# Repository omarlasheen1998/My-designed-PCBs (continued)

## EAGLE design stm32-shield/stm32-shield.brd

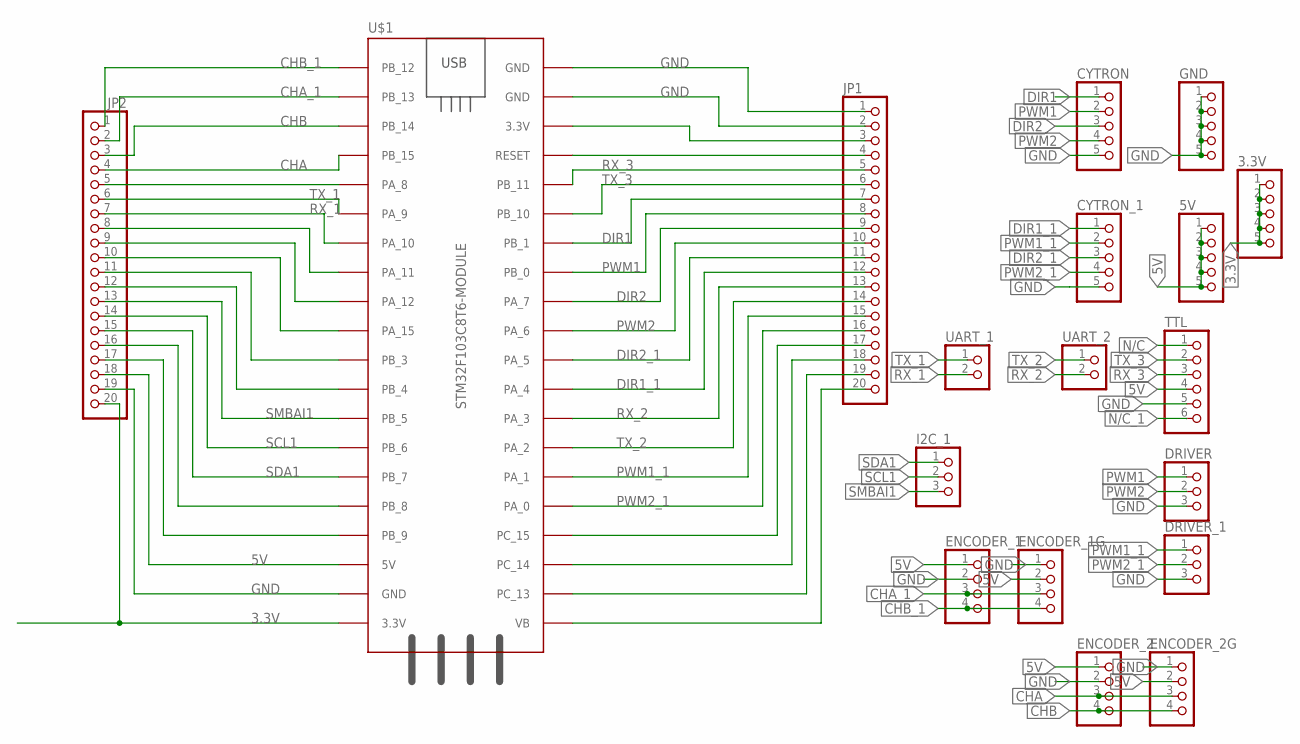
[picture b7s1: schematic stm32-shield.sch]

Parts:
3.3V, 5V: PINHD-1X5; 1X05
CYTRON: PINHD-1X5; 1X05
CYTRON_1: PINHD-1X5; 1X05
DRIVER: PINHD-1X3; 1X03
DRIVER_1: PINHD-1X3; 1X03
ENCODER_1, ENCODER_1G, ENCODER_2, ENCODER_2G: PINHD-1X4; 1X04
GND: PINHD-1X5; 1X05
I2C_1: PINHD-1X3; 1X03
JP1, JP2: PINHD-1X20; 1X20
TTL: PINHD-1X6; 1X06
U$1: STM32F103C8T6-MODULE
UART_1, UART_2: PINHD-1X2; 1X02

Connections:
3.3V: 3.3V.1, 3.3V.2, 3.3V.3, 3.3V.4, 3.3V.5, JP2.20, U$1.3.3V_1 (3.3V)
5V: 5V.1, 5V.2, 5V.3, 5V.4, 5V.5, ENCODER_1.1, ENCODER_1G.2, ENCODER_2.1, ENCODER_2G.2, JP2.18, TTL.4, U$1.5V
8183: JP2.17, U$1.PB_9
823828: JP2.16, U$1.PB_8
CHA: ENCODER_2.3, ENCODER_2G.3, JP2.4, U$1.PB_15
CHA_1: ENCODER_1.3, ENCODER_1G.3, JP2.2, U$1.PB_13
CHB: ENCODER_2.4, ENCODER_2G.4, JP2.3, U$1.PB_14
CHB_1: ENCODER_1.4, ENCODER_1G.4, JP2.1, U$1.PB_12
DIR1: CYTRON.1, JP1.7, U$1.PB_1
DIR1_1: CYTRON_1.1, JP1.12, U$1.PA_4
DIR2: CYTRON.3, JP1.9, U$1.PA_7
DIR2_1: CYTRON_1.3, JP1.11, U$1.PA_5
GND: CYTRON.5, CYTRON_1.5, DRIVER.3, DRIVER_1.3, ENCODER_1.2, ENCODER_1G.1, ENCODER_2.2, ENCODER_2G.1, GND.1, GND.2, GND.3, GND.4, GND.5, JP1.1, JP1.2, JP2.19, TTL.5, U$1.GND_1 (GND), U$1.GND_2 (GND), U$1.GND_3 (GND)
unnamed: JP1.3, U$1.3.3V_2 (3.3V)
unnamed: JP1.4, U$1.RESET
unnamed: JP1.17, U$1.PC_15
unnamed: JP1.18, U$1.PC_14
unnamed: JP1.19, U$1.PC_13
unnamed: JP1.20, U$1.VB
unnamed: JP2.5, U$1.PA_8
unnamed: JP2.8, U$1.PA_11
unnamed: JP2.9, U$1.PA_12
unnamed: JP2.10, U$1.PA_15
unnamed: JP2.11, U$1.PB_3
unnamed: JP2.12, U$1.PB_4
N/C: TTL.1
N/C_1: TTL.6
PWM1: CYTRON.2, DRIVER.1, JP1.8, U$1.PB_0
PWM1_1: CYTRON_1.2, DRIVER_1.1, JP1.15, U$1.PA_1
PWM2: CYTRON.4, DRIVER.2, JP1.10, U$1.PA_6
PWM2_1: CYTRON_1.4, DRIVER_1.2, JP1.16, U$1.PA_0
RX_1: JP2.7, U$1.PA_10, UART_1.2
RX_2: JP1.13, U$1.PA_3, UART_2.2
RX_3: JP1.5, TTL.3, U$1.PB_11
SCL1: I2C_1.2, JP2.14, U$1.PB_6
SDA1: I2C_1.1, JP2.15, U$1.PB_7
SMBAI1: I2C_1.3, JP2.13, U$1.PB_5
TX_1: JP2.6, U$1.PA_9, UART_1.1
TX_2: JP1.14, U$1.PA_2, UART_2.1
TX_3: JP1.6, TTL.2, U$1.PB_10

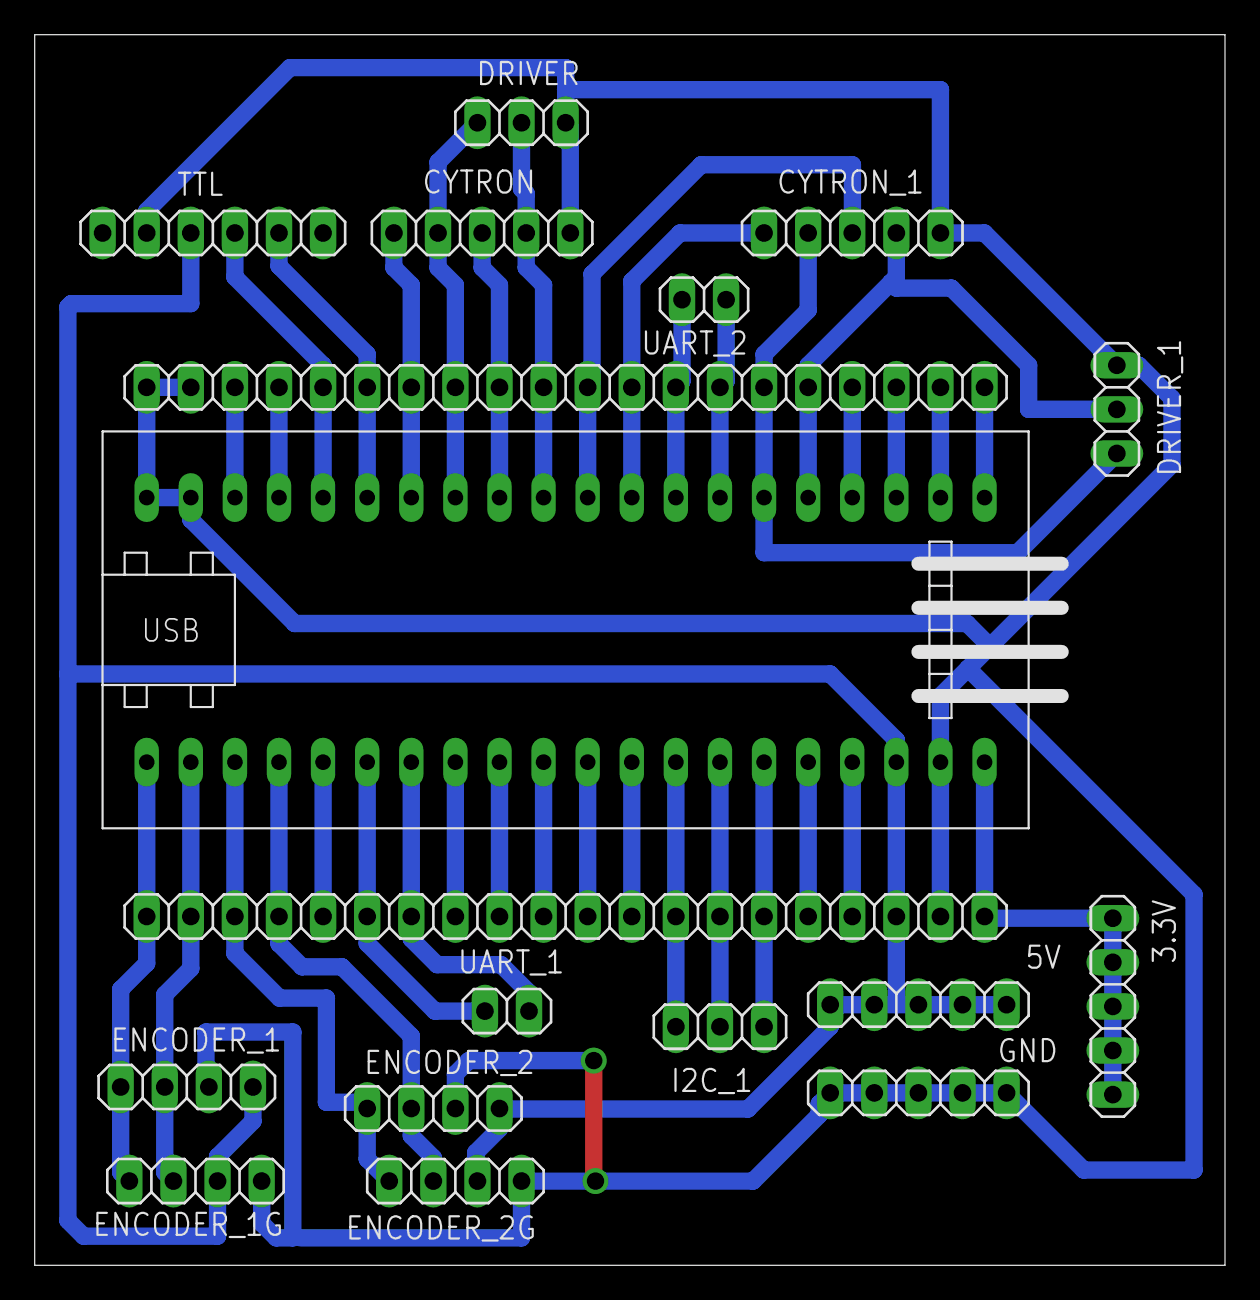
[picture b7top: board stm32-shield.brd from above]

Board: 2 copper layers, 68.6 x 70.9 mm, 18 parts (0 on the bottom side), 38 nets.

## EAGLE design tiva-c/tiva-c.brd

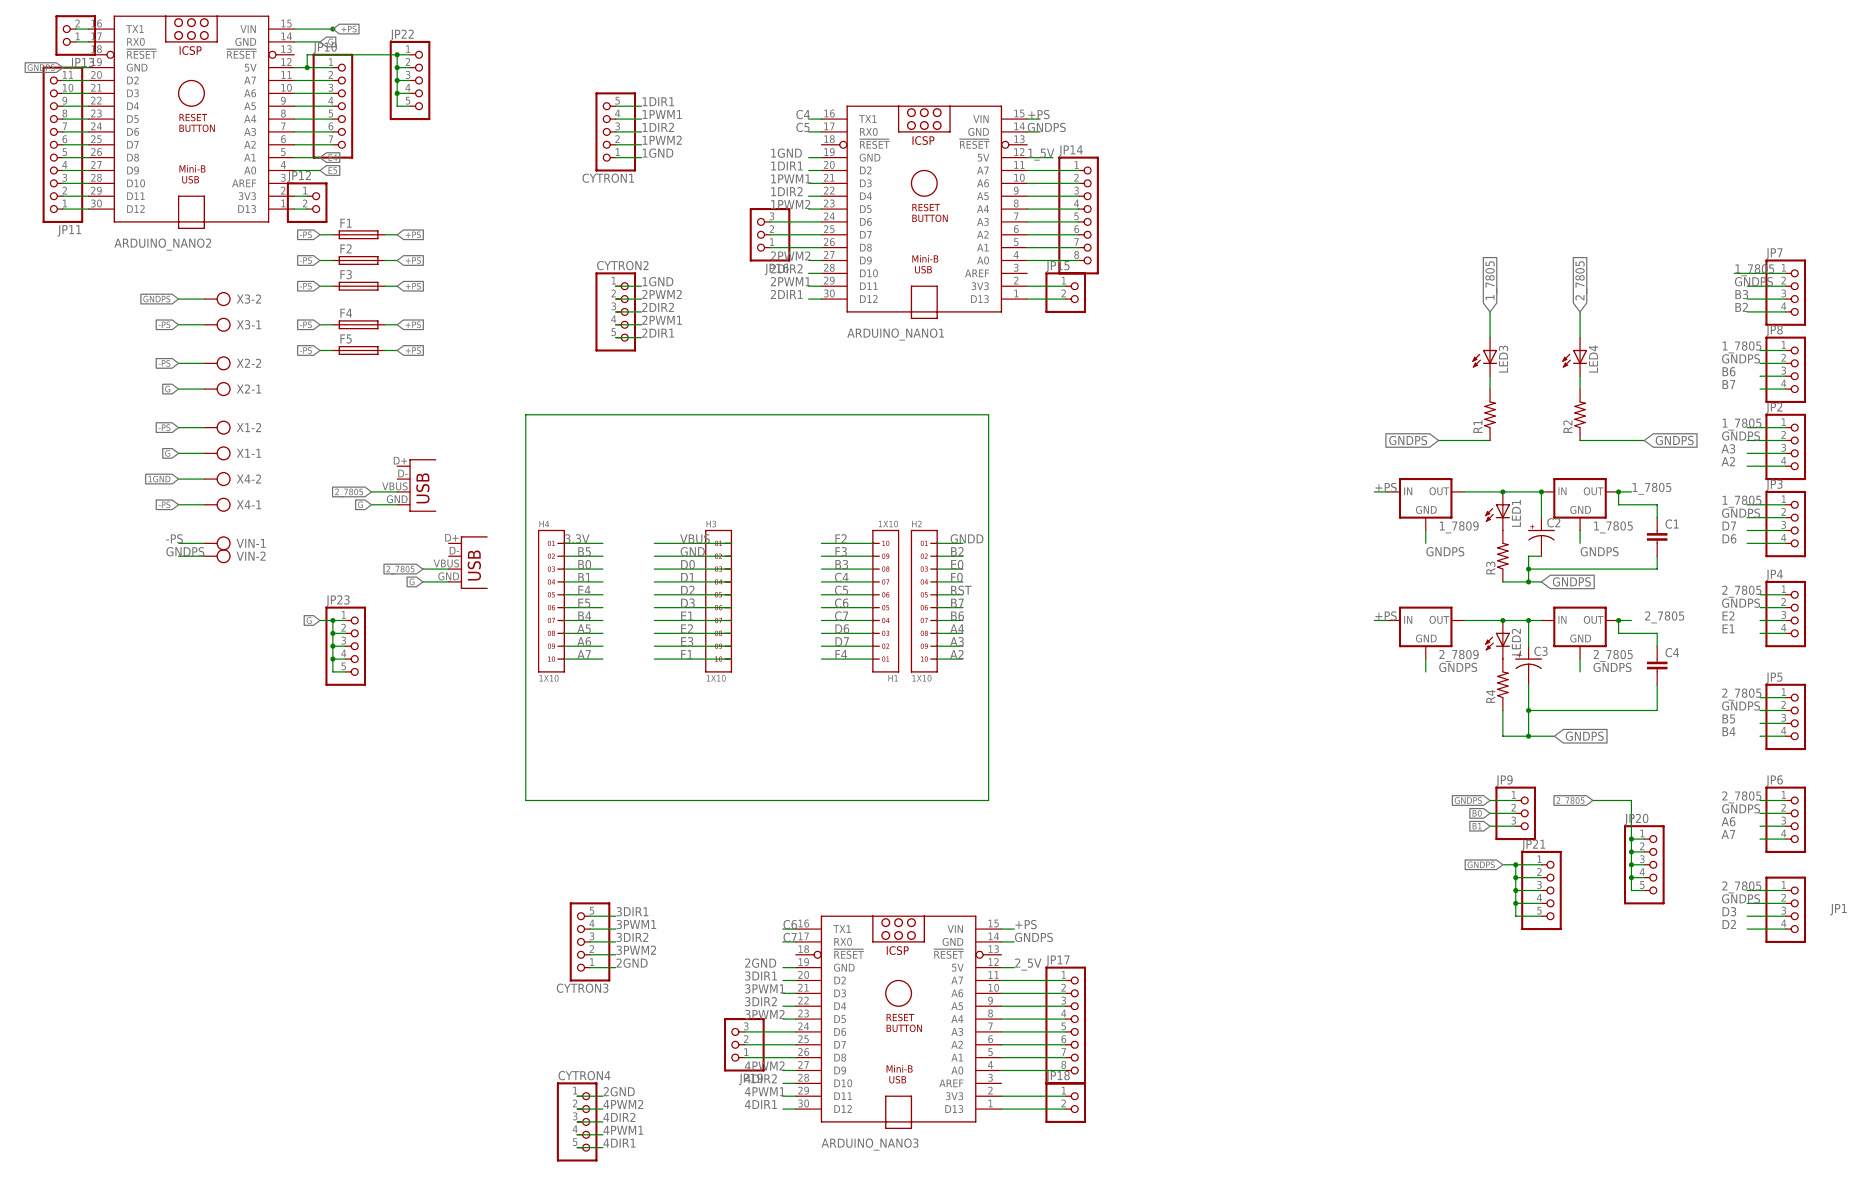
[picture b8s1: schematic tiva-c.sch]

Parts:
1_7805, 1_7809, 2_7805, 2_7809: 78XXS
ARDUINO_NANO1, ARDUINO_NANO2, ARDUINO_NANO3: ARDUINO_NANO
C1, C4: C-EU025-030X050; C025-030X050
C2, C3: CPOL-USE2.5-5; E2,5-5
CYTRON1, CYTRON2, CYTRON3, CYTRON4: PINHD-1X5; 1X05
F1, F2, F3, F4, F5: SH22,5A
H1, H2, H3, H4: 1X10
JP1, JP2, JP3, JP4, JP5, JP6, JP7, JP8: PINHD-1X4; 1X04
JP9, JP16, JP19: PINHD-1X3; 1X03
JP10: PINHD-1X7; 1X07
JP11: PINHD-1X11; 1X11
JP12, JP13, JP15, JP18: PINHD-1X2; 1X02
JP14, JP17: PINHD-1X8; 1X08
JP20, JP21, JP22, JP23: PINHD-1X5; 1X05
LED1, LED2, LED3, LED4: LED5MM
R1, R2, R3, R4: R-US_0204/5; 0204/5
VIN: AK300/2
X1, X2, X3, X4: AK300/2
X5, X6: USB-A-H

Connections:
1DIR1: ARDUINO_NANO1.20 (D2), CYTRON1.5
1DIR2: ARDUINO_NANO1.22 (D4), CYTRON1.3
1GND: ARDUINO_NANO1.19 (GND), CYTRON1.1, CYTRON2.1, X4.2
1PWM1: ARDUINO_NANO1.21 (D3), CYTRON1.4
1PWM2: ARDUINO_NANO1.23 (D5), CYTRON1.2
1_5V: ARDUINO_NANO1.12 (5V)
1_7805: 1_7805.OUT, C1.1, JP2.1, JP3.1, JP7.1, JP8.1, LED3.A
2DIR1: ARDUINO_NANO1.30 (D12), CYTRON2.5
2DIR2: ARDUINO_NANO1.28 (D10), CYTRON2.3
2GND: ARDUINO_NANO3.19 (GND), CYTRON3.1, CYTRON4.1
2PWM1: ARDUINO_NANO1.29 (D11), CYTRON2.4
2PWM2: ARDUINO_NANO1.27 (D9), CYTRON2.2
2_5V: ARDUINO_NANO3.12 (5V)
2_7805: 2_7805.OUT, C4.1, JP1.1, JP4.1, JP5.1, JP6.1, JP20.1, JP20.2, JP20.3, JP20.4, JP20.5, LED4.A, X5.VBUS, X6.VBUS
3.3V: H4.1
3DIR1: ARDUINO_NANO3.20 (D2), CYTRON3.5
3DIR2: ARDUINO_NANO3.22 (D4), CYTRON3.3
3PWM1: ARDUINO_NANO3.21 (D3), CYTRON3.4
3PWM2: ARDUINO_NANO3.23 (D5), CYTRON3.2
4DIR1: ARDUINO_NANO3.30 (D12), CYTRON4.5
4DIR2: ARDUINO_NANO3.28 (D10), CYTRON4.3
4PWM1: ARDUINO_NANO3.29 (D11), CYTRON4.4
4PWM2: ARDUINO_NANO3.27 (D9), CYTRON4.2
+PS: 1_7809.IN, 2_7809.IN, ARDUINO_NANO1.15 (VIN), ARDUINO_NANO2.15 (VIN), ARDUINO_NANO3.15 (VIN), F1.2, F2.2, F3.2, F4.2, F5.2
-PS: F1.1, F2.1, F3.1, F4.1, F5.1, VIN.1, X1.2, X2.2, X3.1, X4.1
A2: H2.10, JP2.4
A3: H2.9, JP2.3
A4: H2.8
A5: H4.8
A6: H4.9, JP6.3
A7: H4.10, JP6.4
B0: H4.3, JP9.2
B1: H4.4, JP9.3
B2: H2.2, JP7.4
B3: H1.8, JP7.3
B4: H4.7, JP5.4
B5: H4.2, JP5.3
B6: H2.7, JP8.3
B7: H2.6, JP8.4
C4: ARDUINO_NANO1.16 (TX1), H1.7
C5: ARDUINO_NANO1.17 (RX0), H1.6
C6: ARDUINO_NANO3.16 (TX1), H1.5
C7: ARDUINO_NANO3.17 (RX0), H1.4
D0: H3.3
D1: H3.4
D2: H3.5, JP1.4
D3: H3.6, JP1.3
D6: H1.3, JP3.4
D7: H1.2, JP3.3
E0: H2.3
E1: H3.7, JP4.4
E2: H3.8, JP4.3
E3: H3.9
E4: ARDUINO_NANO2.5 (A1), H4.5
E5: ARDUINO_NANO2.4 (A0), H4.6
F0: H2.4
F1: H3.10
F2: H1.10
F3: H1.9
F4: H1.1
G: ARDUINO_NANO2.14 (GND), JP23.1, JP23.2, JP23.3, JP23.4, JP23.5, X1.1, X2.1, X5.GND, X6.GND
GND: H3.2
GNDD: H2.1
GNDPS: 1_7805.GND, 1_7809.GND, 2_7805.GND, 2_7809.GND, ARDUINO_NANO1.14 (GND), ARDUINO_NANO2.19 (GND), ARDUINO_NANO3.14 (GND), C1.2, C2.-, C3.-, C4.2, JP1.2, JP2.2, JP3.2, JP4.2, JP5.2, JP6.2, JP7.2, JP8.2, JP9.1, JP21.1, JP21.2, JP21.3, JP21.4, JP21.5, R1.1, R2.1, R3.1, R4.1, VIN.2, X3.2
unnamed: 2_7805.IN, 2_7809.OUT, C3.+, LED2.A
unnamed: 1_7805.IN, 1_7809.OUT, C2.+, LED1.A
unnamed: LED3.K (C), R1.2
unnamed: LED4.K (C), R2.2
unnamed: LED1.K (C), R3.2
unnamed: LED2.K (C), R4.2
unnamed: ARDUINO_NANO2.2 (3V3), JP12.1
unnamed: ARDUINO_NANO2.11 (A7), JP10.2
unnamed: ARDUINO_NANO2.10 (A6), JP10.3
unnamed: ARDUINO_NANO2.9 (A5), JP10.4
unnamed: ARDUINO_NANO2.8 (A4), JP10.5
unnamed: ARDUINO_NANO2.7 (A3), JP10.6
unnamed: ARDUINO_NANO2.6 (A2), JP10.7
unnamed: ARDUINO_NANO2.30 (D12), JP11.1
unnamed: ARDUINO_NANO2.29 (D11), JP11.2
unnamed: ARDUINO_NANO2.28 (D10), JP11.3
unnamed: ARDUINO_NANO2.27 (D9), JP11.4
unnamed: ARDUINO_NANO2.26 (D8), JP11.5
unnamed: ARDUINO_NANO2.25 (D7), JP11.6
unnamed: ARDUINO_NANO2.24 (D6), JP11.7
unnamed: ARDUINO_NANO2.23 (D5), JP11.8
unnamed: ARDUINO_NANO2.22 (D4), JP11.9
unnamed: ARDUINO_NANO2.21 (D3), JP11.10
unnamed: ARDUINO_NANO2.20 (D2), JP11.11
unnamed: ARDUINO_NANO2.1 (D13), JP12.2
unnamed: ARDUINO_NANO2.17 (RX0), JP13.1
unnamed: ARDUINO_NANO2.16 (TX1), JP13.2
unnamed: ARDUINO_NANO1.11 (A7), JP14.1
unnamed: ARDUINO_NANO1.10 (A6), JP14.2
unnamed: ARDUINO_NANO1.9 (A5), JP14.3
unnamed: ARDUINO_NANO1.8 (A4), JP14.4
unnamed: ARDUINO_NANO1.7 (A3), JP14.5
unnamed: ARDUINO_NANO1.6 (A2), JP14.6
unnamed: ARDUINO_NANO1.5 (A1), JP14.7
unnamed: ARDUINO_NANO1.4 (A0), JP14.8
unnamed: ARDUINO_NANO1.2 (3V3), JP15.1
unnamed: ARDUINO_NANO1.1 (D13), JP15.2
unnamed: ARDUINO_NANO1.26 (D8), JP16.1
unnamed: ARDUINO_NANO1.25 (D7), JP16.2
unnamed: ARDUINO_NANO1.24 (D6), JP16.3
unnamed: ARDUINO_NANO3.11 (A7), JP17.1
unnamed: ARDUINO_NANO3.10 (A6), JP17.2
unnamed: ARDUINO_NANO3.9 (A5), JP17.3
unnamed: ARDUINO_NANO3.8 (A4), JP17.4
unnamed: ARDUINO_NANO3.7 (A3), JP17.5
unnamed: ARDUINO_NANO3.6 (A2), JP17.6
unnamed: ARDUINO_NANO3.5 (A1), JP17.7
unnamed: ARDUINO_NANO3.4 (A0), JP17.8
unnamed: ARDUINO_NANO3.2 (3V3), JP18.1
unnamed: ARDUINO_NANO3.1 (D13), JP18.2
unnamed: ARDUINO_NANO3.26 (D8), JP19.1
unnamed: ARDUINO_NANO3.25 (D7), JP19.2
unnamed: ARDUINO_NANO3.24 (D6), JP19.3
unnamed: ARDUINO_NANO2.12 (5V), JP10.1, JP22.1, JP22.2, JP22.3, JP22.4, JP22.5
RST: H2.5
VBUS: H3.1

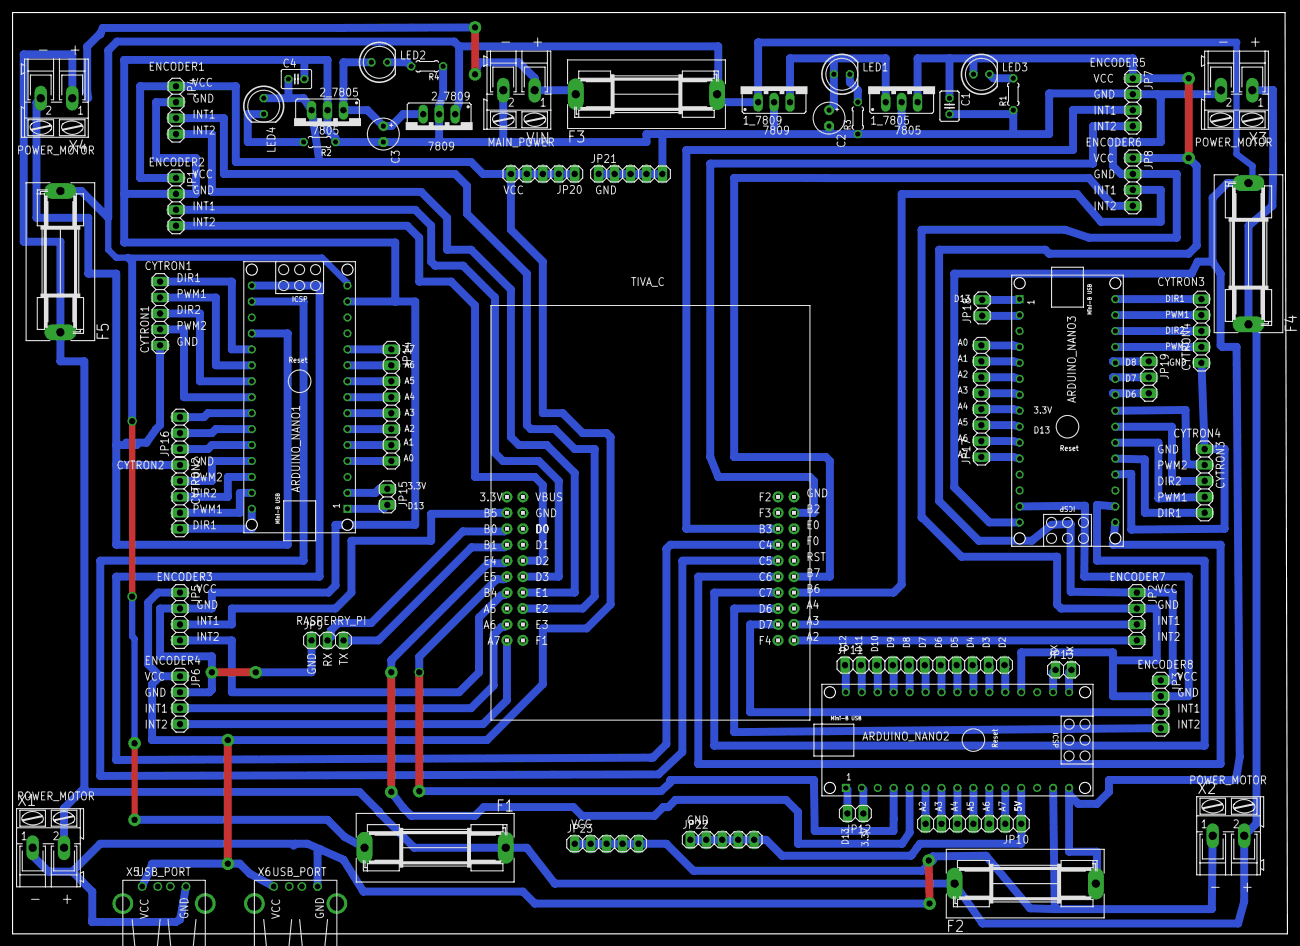
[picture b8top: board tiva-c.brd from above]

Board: 2 copper layers, 203.1 x 146.7 mm, 62 parts (0 on the bottom side), 102 nets.
